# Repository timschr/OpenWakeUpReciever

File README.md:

# README - Open Wake-Up Receiver (WuR) Platform

## Table of Contents
1. [Introduction](#introduction)
2. [Getting Started](#getting-started)
3. [Documentation](#documentation)
4. [Usage](#usage)
5. [Contributing](#contributing)
6. [FAQ](#faq)
7. [License](#license)
8. [Acknowledgments](#acknowledgments)

## Introduction

Welcome to the world of Wake-up Receivers (WuRs)! 

Have you ever wished to have a tiny, ultra-low power device that can awaken your sensor nodes from sleep mode only when needed, saving power and reducing latency? WuR is the game-changer you've been waiting for!
The wake-up receiver's job is to keep a power-hungry device asleep and only wake it up when it's needed, saving energy.

This technology can be the brain of your next IoT project, enabling wireless sensor networks to function efficiently, conserve energy, and respond swiftly. From setting up a smart home system that wakes up when you're near, to implementing precision agriculture that responds to real-time changes in the environment, WuR opens up a world of possibilities.

## How to get started
Just head over to the [Hardware Guide](hardware/README.md) and go step by step from there.
If you feel at any point that your need more background or explation why thing where done the way the are, please refer to the [thesis](master_thesis_open_wake_up_receiver.pdf) this project is based on.

## How to get done

#### 1. Order Your PCB

The first step is to order your PCB (Printed Circuit Board). This will serve as the base for your wake-up receiver, where you'll attach and connect all your components. 

#### 2. Acquire Necessary Parts

Next, you'll need to gather all the other parts required for this project. This includes an 868MHz antenna a nano power comparator, and the PIC12LF1552 Microcontroller Unit (MCU). You can refer to the [Hardware Guide](hardware/README.md) for a more detailed list and where to get these parts.

#### 3. Assemble Your Receiver

Once you have your PCB and all the necessary parts, you can start putting your receiver together. Attach the components to your PCB and connect them according to the circuit design. Remember to double-check all your connections to ensure they're correct and secure.

#### 4. Program the MCU

With your circuit assembled, it's time to program your MCU. You'll need to flash the provided software onto the PIC12LF1552 using suitable PIC microcontroller programming software. More details on how to do this can be found in the [Software Guide](software/README.md).

#### 5. Acquire a Transmitter

Finally, you'll need a transmitter capable of sending OOK (On-Off Keying) signals at 868MHz. This will be used to send the wake-up signal to your receiver. The only requirements are that the transmitter can operate at this frequency and use OOK modulation.

### Prerequisites

#### Hardware:
  - PCB (Printed Circuit Board)
  - All the parts
  - 868 OOK Tranceiver
  - Breadboard
    
#### Tools:
- PICKit3: Programming to for PIC microcontroller. With some effort you can also use a simple arduino for this. Explaine e.g. here [https://github.com/jaromir-sukuba/a-p-prog])
- Soldering iron: You'll need this to attach components to your PCB. Not needed when you order the PCB preassembled.
- (Oscilloscope: This is optional but recommended for analyzing the signals in your circuit.)
- (NanoVNA: This is optional but handy to analyze the quality of the mathching network)

## Contributing

We warmly welcome contributions to this project. If you'd like to contribute, please fork the repository and make your changes. Then create a Pull Request to get your changes merged and reviewed.

We have a few guidelines for contributing, please check them out here: [CONTRIBUTING.md](./CONTRIBUTING.md)

## License

This project is licensed under the MIT License - see the [LICENSE.md](LICENSE.md) file for details

## Acknowledgments

I'd like to acknowledge the contributions of my academic advisors and the open-source community that has been pivotal in making this project what it is.

---

To create a detailed `CONTRIBUTING.md` file, include sections like:

1. Code of Conduct
2. How to report bugs or request features
3. How to set up the development environment
4. Code style guides
5. How to submit a Pull Request
6. What to expect after a Pull Request is submitted

In the `LICENSE.md` file, provide the full text of the license. If you're using MIT, you can find that [here](https://choosealicense.com/licenses/mit/).

The FAQ section should be updated as users interact with your project. Start with questions you think will be common, then add more as they come up.

Remember, READMEs are often the first thing people see when they come to your project, so make it engaging, informative, and welcoming.

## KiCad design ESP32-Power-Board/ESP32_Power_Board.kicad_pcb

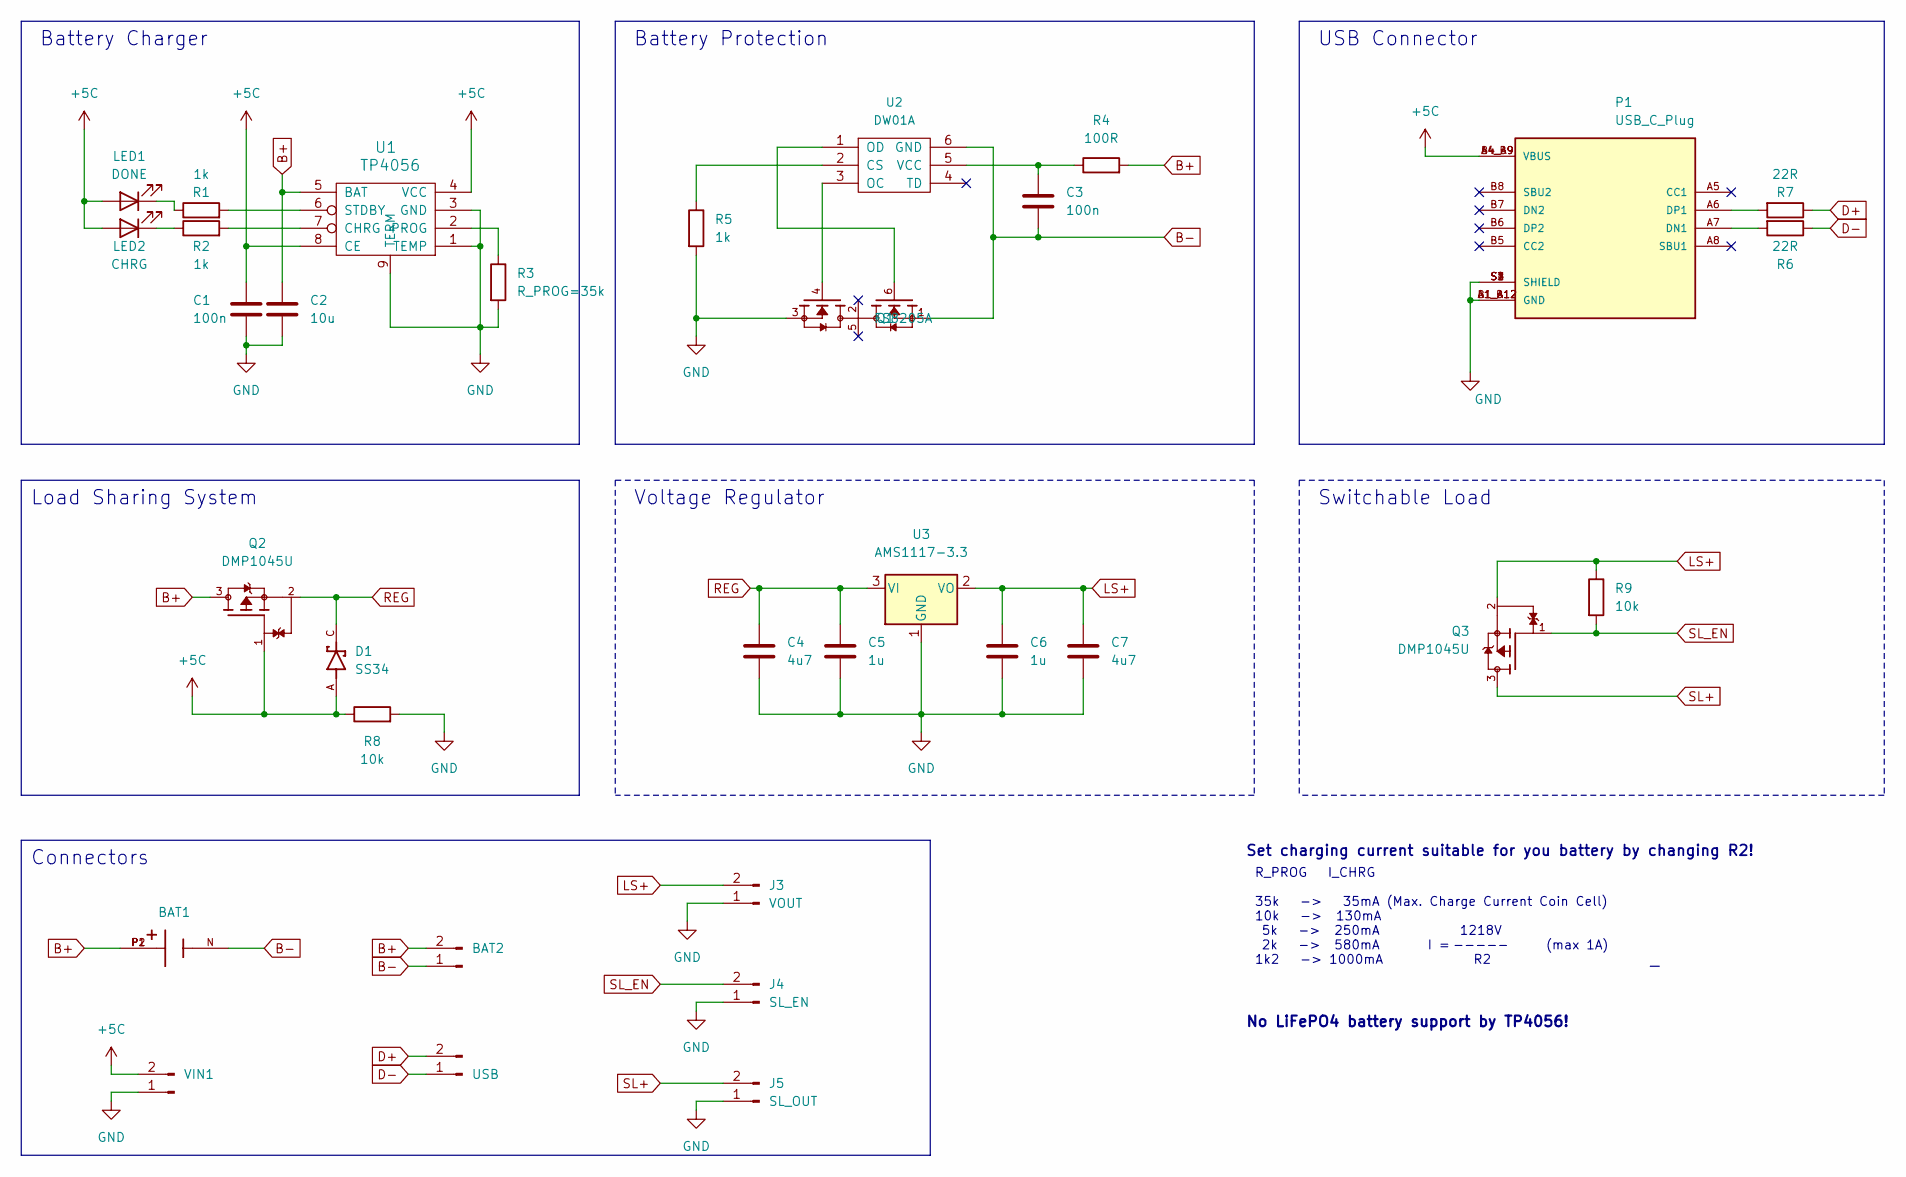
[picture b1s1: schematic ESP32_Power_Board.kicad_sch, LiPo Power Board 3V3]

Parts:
BAT1: BAT-HLD-005-THM; BAT_BAT-HLD-005-THM; PARTREV A
BAT2: BAT; JST_PH_B2B-PH-K_1x02_P2.00mm_Vertical
C1, C3: 100n; C_0805_2012Metric
C2: 10u; C_0805_2012Metric
C4, C7: 4u7; C_0805_2012Metric
C5, C6: 1u; C_0805_2012Metric
D1: SS34; DIOM7959X265N; PARTREV 31 Aug 2016
J3: VOUT; PinHeader_1x02_P2.54mm_Vertical
J4: SL_EN; PinHeader_1x02_P2.54mm_Vertical
J5: SL_OUT; PinHeader_1x02_P2.54mm_Vertical
LED1: DONE; LED_0805_2012Metric
LED2: CHRG; LED_0805_2012Metric
P1: USB_C_Plug; HRO_TYPE-C-31-M-12; PARTREV 2020.12.08
Q1: FS8205A; SOT95P280X145-6N; PARTREV 1.9
Q2, Q3: DMP1045U; SOT91P240X110-3N; PARTREV 7 - 2
R1, R2, R5: 1k; R_0805_2012Metric
R3: R_PROG=35k; R_0805_2012Metric
R4: 100R; R_0805_2012Metric
R6, R7: 22R; R_0805_2012Metric
R8, R9: 10k; R_0805_2012Metric
U1: TP4056; SOP127P600X175-9N
U2: DW01A; SOT23-6
U3: AMS1117-3.3; SOT-223-3_TabPin2
USB1: USB; PinSocket_1x02_P2.54mm_Vertical
VIN1: +VIN-; PinHeader_1x02_P2.54mm_Vertical

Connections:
+5C: C1.1, D1.A, LED1.2 (A), LED2.2 (A), P1.A4_B9 (VBUS), P1.B4_A9 (VBUS), Q2.1, R8.1, U1.4 (VCC), U1.8 (CE), VIN1.2
B+: BAT1.P1, BAT1.P2, BAT2.2, C2.1, Q2.3, R4.2, U1.5 (BAT)
B-: BAT1.N, BAT2.1, C3.2, Q1.1, U2.6 (GND)
D+: R7.1, USB1.2
D-: R6.1, USB1.1
GND: C1.2, C2.2, C4.2, C5.2, C6.2, C7.2, J3.1, J4.1, J5.1, P1.A1_B12 (GND), P1.B1_A12 (GND), P1.S1 (SHIELD), P1.S2 (SHIELD), P1.S3 (SHIELD), P1.S4 (SHIELD), Q1.3, R3.2, R5.2, R8.2, U1.1 (TEMP), U1.3 (GND), U1.9 (TERM), U3.1 (GND), VIN1.1; also elsewhere on the board
LS+: C6.1, C7.1, J3.2, Q3.2, R9.1, U3.2 (VO)
unnamed: C3.1, R4.1, U2.5 (VCC)
unnamed: LED1.1 (K), R1.1
unnamed: LED2.1 (K), R2.1
unnamed: P1.A6 (DP1), R7.2
unnamed: P1.A7 (DN1), R6.2
unnamed: R1.2, U1.6 (STDBY)
unnamed: R2.2, U1.7 (CHRG)
unnamed 14: R3.1, U1.2 (PROG); also elsewhere on the board
unnamed: R5.1, U2.2 (CS)
unnamed: Q1.6, U2.1 (OD)
unnamed: Q1.4, U2.3 (OC)
REG: C4.1, C5.1, D1.C, Q2.2, U3.3 (VI)
SL+: J5.2, Q3.3
SL_EN: J4.2, Q3.1, R9.2

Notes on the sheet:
Load Sharing System
USB Connector
1218V ----- R2
Switchable Load
Connectors
No LiFePO4 battery support by TP4056!
Battery Protection
Voltage Regulator
R_PROG I_CHRG 35k -> 35mA (Max. Charge Current Coin Cell) 10k -> 130mA 5k -> 250mA 2k -> 580mA I = (max 1A) 1k2 -> 1000mA
Battery Charger
Set charging current suitable for you battery by changing R2!

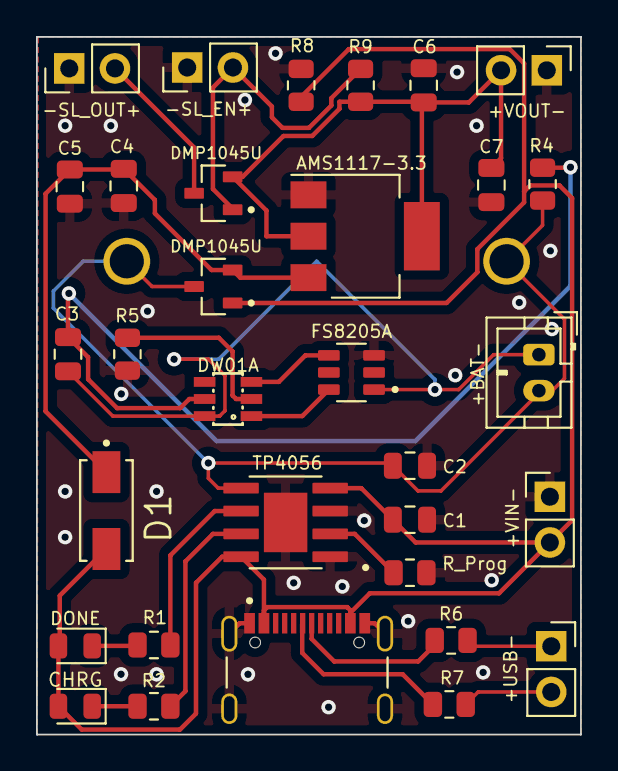
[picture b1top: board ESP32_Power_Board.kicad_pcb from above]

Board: 2 copper layers, 30.2 x 38.8 mm, 33 parts (1 on the bottom side), 21 nets.

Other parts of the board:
R_Prog: 35k; R_0805_2012Metric

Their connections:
GND: R_Prog.2; also elsewhere on the board
unnamed 14: R_Prog.1; also elsewhere on the board

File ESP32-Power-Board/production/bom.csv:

Designator,Footprint,Quantity,Value,LCSC Part #
BAT1,BAT_BAT-HLD-005-THM,1,BAT-HLD-005-THM,
BAT2,JST_PH_B2B-PH-K_1x02_P2.00mm_Vertical,1,+BAT-,
"C1, C3",C_0805_2012Metric,2,100n,
C2,C_0805_2012Metric,1,10u,
"C4, C7",C_0805_2012Metric,2,4u7,
"C5, C6",C_0805_2012Metric,2,1u,
D1,DIOM5226X240N,1,SS34,
J3,PinHeader_1x02_P2.54mm_Vertical,1,+VOUT-,
J4,PinHeader_1x02_P2.54mm_Vertical,1,-SL_EN+,
J5,PinHeader_1x02_P2.54mm_Vertical,1,-SL_OUT+,
LED1,LED_0805_2012Metric,1,DONE,
LED2,LED_0805_2012Metric,1,CHRG,
P1,HRO_TYPE-C-31-M-12,1,USB_C_Plug,
Q1,SOT95P280X145-6N,1,FS8205A,
"Q2, Q3",SOT91P240X110-3N,2,DMP1045U,
"R1, R2, R5",R_0805_2012Metric,3,1k,
R4,R_0805_2012Metric,1,100R,
"R6, R7",R_0805_2012Metric,2,22R,
"R8, R9",R_0805_2012Metric,2,10k,
R_Prog,R_0805_2012Metric,1,35k,
U1,SOP127P600X175-9N,1,TP4056,
U2,SOT23-6,1,DW01A,
U3,SOT-223-3_TabPin2,1,AMS1117-3.3,
USB1,PinSocket_1x02_P2.54mm_Vertical,1,+USB-,
VIN1,PinHeader_1x02_P2.54mm_Vertical,1,+VIN-,

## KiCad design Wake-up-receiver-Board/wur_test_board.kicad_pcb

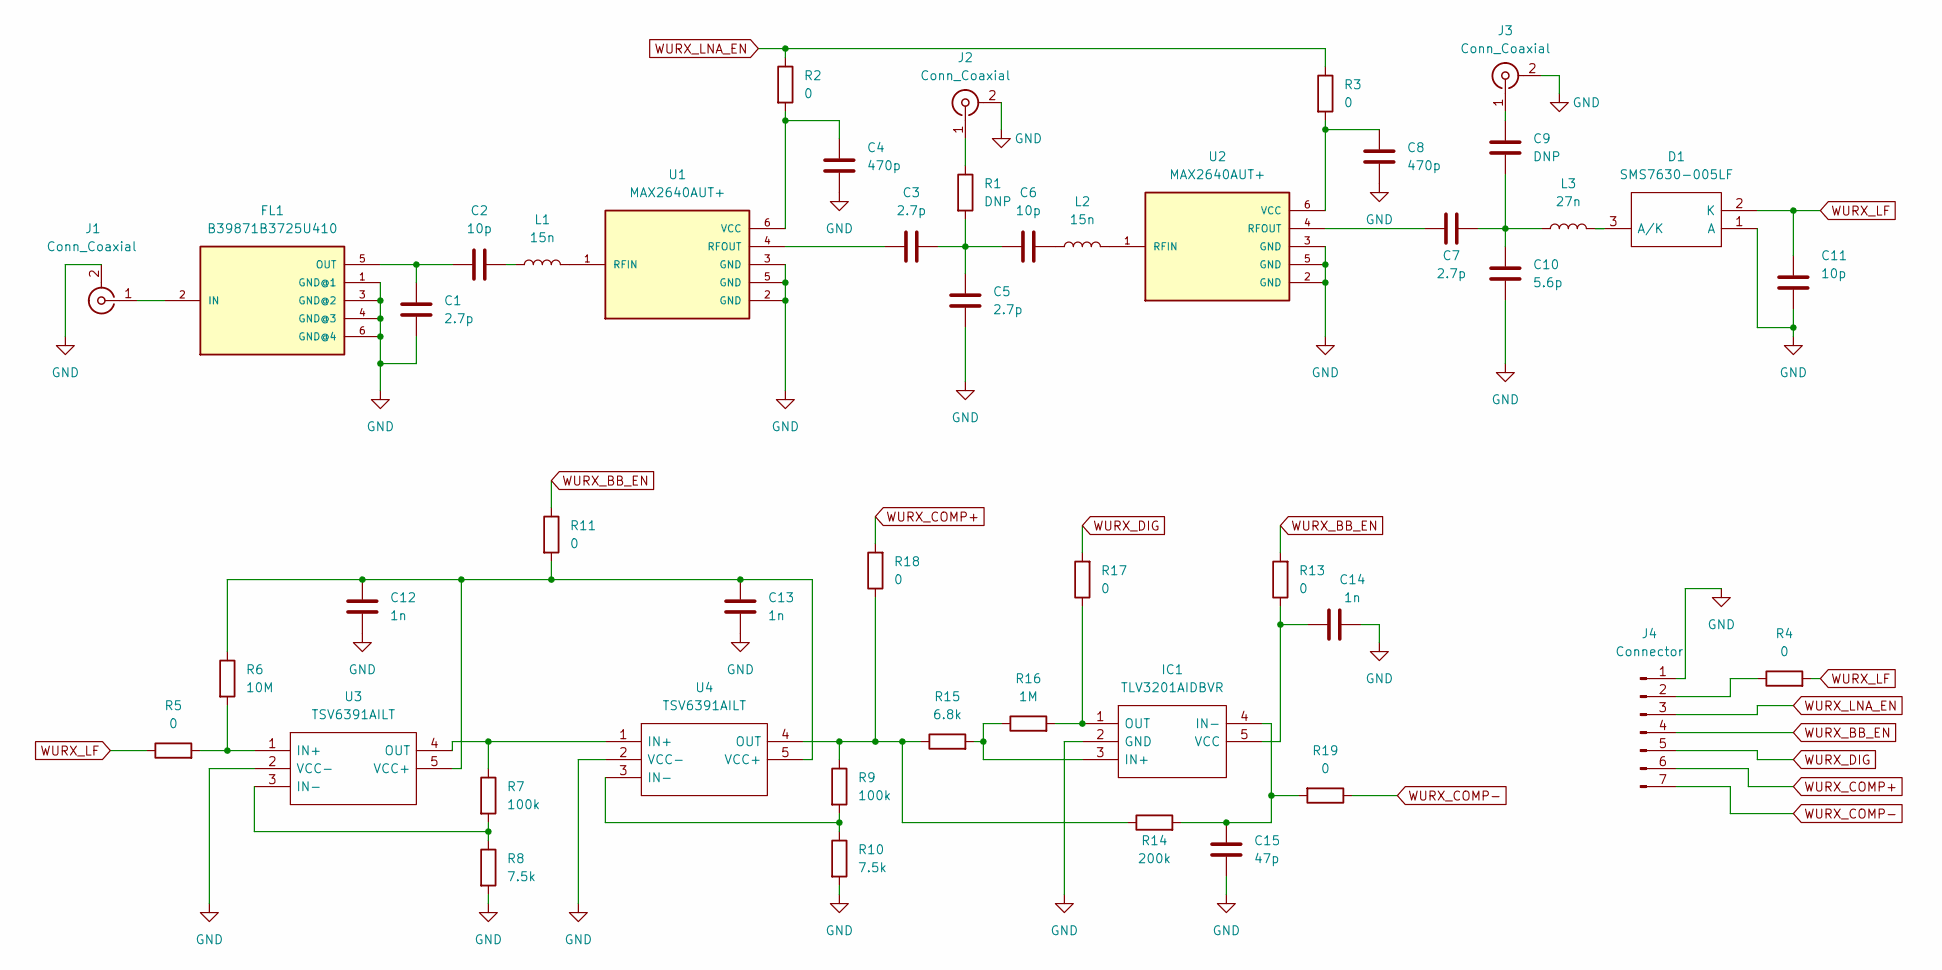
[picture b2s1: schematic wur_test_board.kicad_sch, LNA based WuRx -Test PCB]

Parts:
C1, C3, C5, C7: 2.7p; C_0805_2012Metric
C2, C6, C11: 10p; C_0805_2012Metric
C4, C8: 470p; C_0805_2012Metric
C9: DNP; C_0805_2012Metric
C10: 5.6p; C_0805_2012Metric
C12, C13, C14: 1n; C_0805_2012Metric
C15: 47p; C_0805_2012Metric
D1: SMS7630-005LF; SOT95P237X112-3N; Manufacturer_Part_Number SMS7630-005LF; Mouser Part Number 873-SMS7630-005LF
FL1: B39871B3725U410; SON120P300X300X110-6N
IC1: TLV3201AIDBVR; SOT95P280X145-5N; Manufacturer_Part_Number TLV3201AIDBVR; Mouser Part Number 595-TLV3201AIDBVR
J1: Conn_Coaxial; SMA_Amphenol_901-143_Horizontal
J2, J3: Conn_Coaxial; BNC_Amphenol_B6252HB-NPP3G-50_Horizontal
J4: Connector; PinHeader_1x07_P2.54mm_Vertical
L1, L2: 15n; L_0805_2012Metric
L3: 27n; L_0805_2012Metric
R1: DNP; R_0805_2012Metric
R2, R3, R4, R5, R11, R13, R17, R18, R19: 0; R_0805_2012Metric
R6: 10M; R_0805_2012Metric
R7, R9: 100k; R_0805_2012Metric
R8, R10: 7.5k; R_0805_2012Metric
R14: 200k; R_0805_2012Metric
R15: 6.8k; R_0805_2012Metric
R16: 1M; R_0805_2012Metric
U1, U2: MAX2640AUT+; SOT95P280X145-6N
U3, U4: TSV6391AILT; SOT95P280X145-5N; Manufacturer_Part_Number TSV6391AILT; Mouser Part Number 511-TSV6391AILT

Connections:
GND: C1.1, C4.2, C5.2, C8.2, C10.2, C11.1, C12.2, C13.1, C14.2, C15.2, D1.1 (A), FL1.1 (GND@1), FL1.3 (GND@2), FL1.4 (GND@3), FL1.6 (GND@4), IC1.2 (GND), J1.2 (Ext), J2.2 (Ext), J3.2 (Ext), J4.1, R8.2, R10.2, U1.2 (GND), U1.3 (GND), U1.5 (GND), U2.2 (GND), U2.3 (GND), U2.5 (GND), U3.2 (VCC-), U4.2 (VCC-)
unnamed: C1.2, C2.1, FL1.5 (OUT)
unnamed: C2.2, L1.1
unnamed: C3.1, U1.4 (RFOUT)
unnamed: C3.2, C5.1, C6.1, R1.2
unnamed: C4.1, R2.2, U1.6 (VCC)
unnamed: C6.2, L2.1
unnamed: C7.2, U2.4 (RFOUT)
unnamed: C8.1, R3.2, U2.6 (VCC)
unnamed: C9.1, J3.1 (In)
unnamed: C7.1, C9.2, C10.1, L3.1
unnamed: C12.1, C13.2, R6.1, R11.2, U3.5 (VCC+), U4.5 (VCC+)
unnamed: C14.1, IC1.5 (VCC), R13.1
unnamed: C15.1, IC1.4 (IN-), R14.2, R19.2
unnamed: D1.3 (A/K), L3.2
unnamed: FL1.2 (IN), J1.1 (In)
unnamed: IC1.1 (OUT), R16.2, R17.1
unnamed: IC1.3 (IN+), R15.2, R16.1
unnamed: J2.1 (In), R1.1
unnamed: J4.2, R4.1
unnamed: L1.2, U1.1 (RFIN)
unnamed: L2.2, U2.1 (RFIN)
unnamed: R5.2, R6.2, U3.1 (IN+)
unnamed: R7.1, U3.4 (OUT), U4.1 (IN+)
unnamed: R7.2, R8.1, U3.3 (IN-)
unnamed: R9.2, R10.1, U4.3 (IN-)
unnamed: R9.1, R14.1, R15.1, R18.1, U4.4 (OUT)
WURX_BB_EN: J4.4, R11.1, R13.2
WURX_COMP+: J4.6, R18.2
WURX_COMP-: J4.7, R19.1
WURX_DIG: J4.5, R17.2
WURX_LF: C11.2, D1.2 (K), R4.2, R5.1
WURX_LNA_EN: J4.3, R2.1, R3.1

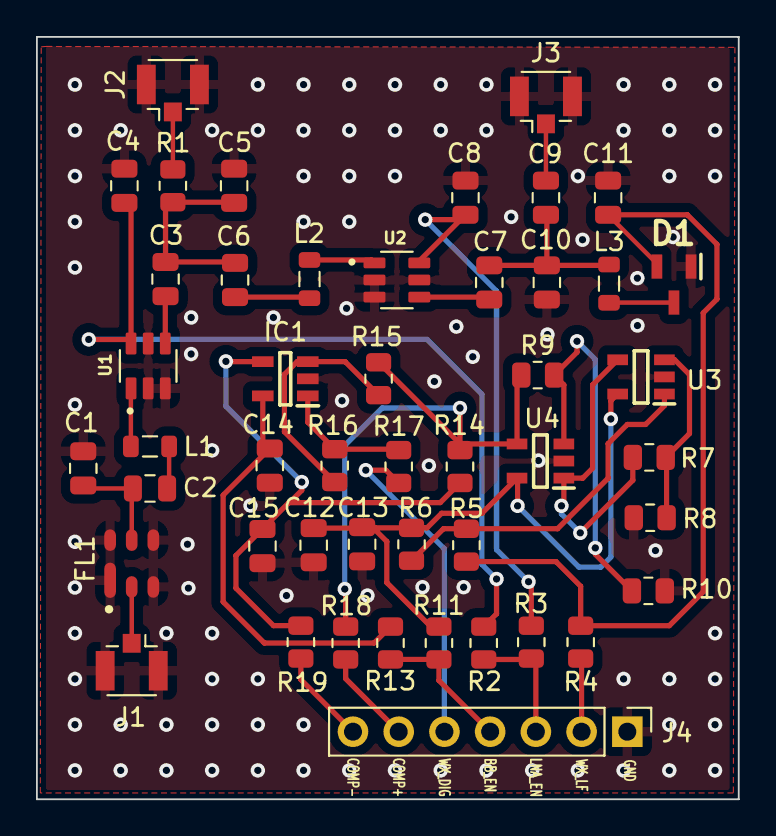
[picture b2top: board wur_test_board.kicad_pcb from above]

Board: 4 copper layers, 39.0 x 42.4 mm, 47 parts (0 on the bottom side), 33 nets.

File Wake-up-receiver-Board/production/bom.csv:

Designator,Footprint,Quantity,Value,LCSC Part #
"C1, C3, C5, C7",C_0805_2012Metric,4,2.7p,
C10,C_0805_2012Metric,1,5.6p,
"C11, C2, C6",C_0805_2012Metric,3,10p,
"C12, C13, C14",C_0805_2012Metric,3,1n,
C15,C_0805_2012Metric,1,47p,
"C4, C8",C_0805_2012Metric,2,470p,
C9,C_0805_2012Metric,1,DNP,
D1,SOT95P237X112-3N,1,SMS7630-005LF,
FL1,SON120P300X300X110-6N,1,B39871B3725U410,
IC1,SOT95P280X145-5N,1,TLV3201AIDBVR,
"J1, J2, J3",U.FL_Hirose_U.FL-R-SMT-1_Vertical,3,Conn_Coaxial,
J4,PinHeader_1x07_P2.54mm_Vertical,1,Connector,
"L1, L2",L_0805_2012Metric,2,15n,
L3,L_0805_2012Metric,1,27n,
R1,R_0805_2012Metric,1,DNP,
"R10, R8",R_0805_2012Metric,2,7.5k,
"R11, R13, R17, R18, R19, R2, R3, R4, R5",R_0805_2012Metric,9,0,
R14,R_0805_2012Metric,1,200k,
R15,R_0805_2012Metric,1,6.8k,
R16,R_0805_2012Metric,1,1M,
R6,R_0805_2012Metric,1,10M,
"R7, R9",R_0805_2012Metric,2,100k,
"U1, U2",SOT95P280X145-6N,2,MAX2640AUT+,
"U3, U4",SOT95P280X145-5N,2,TSV6391AILT,

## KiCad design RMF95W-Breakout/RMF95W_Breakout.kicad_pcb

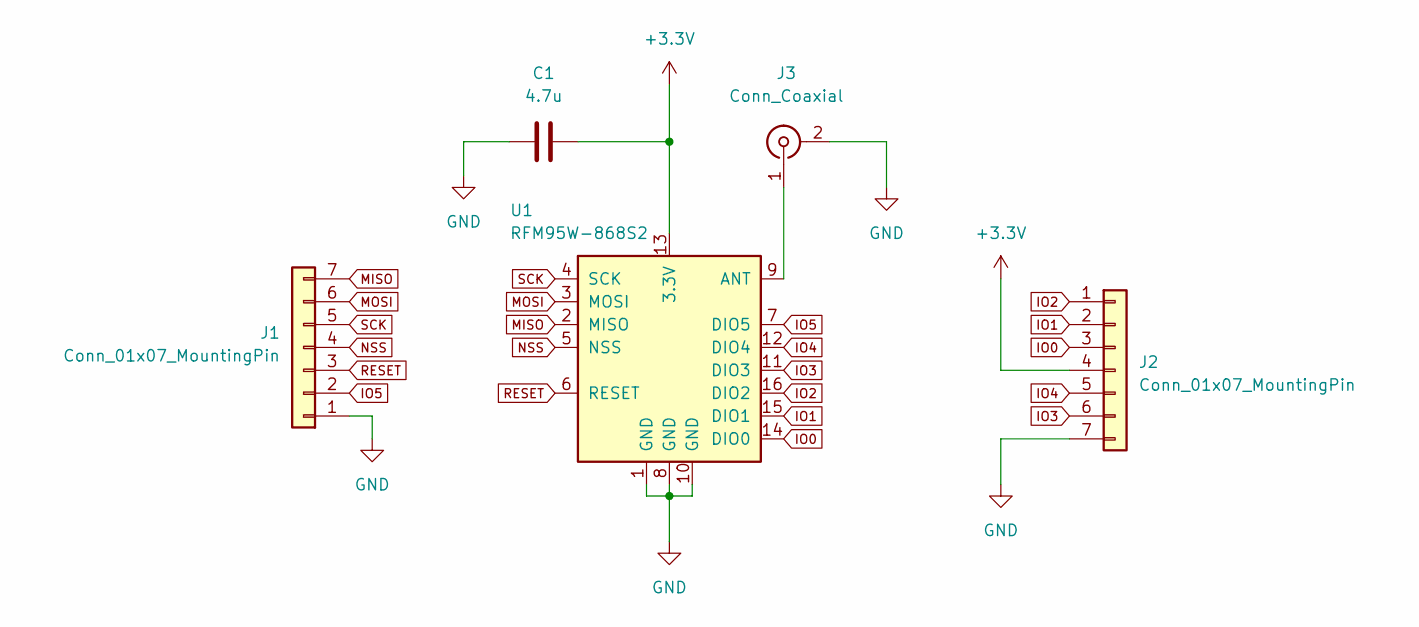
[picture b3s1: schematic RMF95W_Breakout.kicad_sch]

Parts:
C1: 4.7u; C_0805_2012Metric
J1, J2: Conn_01x07_MountingPin; PinHeader_1x07_P2.54mm_Vertical
J3: Conn_Coaxial; U.FL_Hirose_U.FL-R-SMT-1_Vertical
U1: RFM95W-868S2; HOPERF_RFM9XW_SMD

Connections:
+3.3V: C1.2, J2.4, U1.13 (3.3V)
GND: C1.1, J1.1, J2.7, J3.2 (Ext), U1.1 (GND), U1.8 (GND), U1.10 (GND)
IO0: J2.3, U1.14 (DIO0)
IO1: J2.2, U1.15 (DIO1)
IO2: J2.1, U1.16 (DIO2)
IO3: J2.6, U1.11 (DIO3)
IO4: J2.5, U1.12 (DIO4)
IO5: J1.2, U1.7 (DIO5)
MISO: J1.7, U1.2 (MISO)
MOSI: J1.6, U1.3 (MOSI)
NSS: J1.4, U1.5 (NSS)
unnamed: J3.1 (In), U1.9 (ANT)
RESET: J1.3, U1.6 (RESET)
SCK: J1.5, U1.4 (SCK)

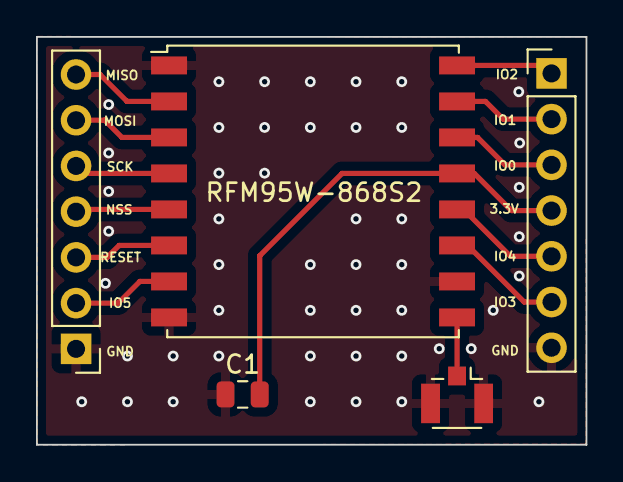
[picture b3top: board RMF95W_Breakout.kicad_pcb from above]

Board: 4 copper layers, 30.5 x 22.7 mm, 5 parts (0 on the bottom side), 14 nets.

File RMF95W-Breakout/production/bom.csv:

Designator,Footprint,Quantity,Value,LCSC Part #
C1,C_0805_2012Metric,1,4.7u,
"J1, J2",PinHeader_1x07_P2.54mm_Vertical,2,Conn_01x07_MountingPin,
J3,U.FL_Hirose_U.FL-R-SMT-1_Vertical,1,Conn_Coaxial,
U1,HOPERF_RFM9XW_SMD,1,RFM95W-868S2,

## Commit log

2023-01-05 ainit upload: ototyping boards
2023-07-03 Create LICENSE
2023-07-03 Rename software_guide.md to software/software_guide.md
2023-07-03 Rename software_guide.md to README.md
